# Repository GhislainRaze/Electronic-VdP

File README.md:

# An electronic Van der Pol/Duffing oscillator

## Overview
This repository contains files for the realization of an electronic Van der Pol/Duffing oscillator, i.e., a circuit whose behavior is governed the equation

$\qquad m\ddot{x}(t) + (\mu x^2(t)+c)\dot{x}(t) + kx(t) + k_3 x^3(t) = f_{ext}(t),$
    
with $m>0$ and $k_3\geq0$.

The circuit takes a signal proportional to $f_{ext}$ and the parameters $c$ and $\mu$ as input and outputs signals proportional to $x$ and $\dot{x}$. It allows for tunable values of the parameters $k$ and $k_3$ via the use of potentiometers. It is also possible to chose positive or negative values for $k$ and obtain a single- or double-well oscillator, respectively.

The circuit requires an external power source with symmetric supplies. The input and output signals can be imposed/measured with BNC connectors.

## References

The circuit diagrams were realized using KiCad7.0 (https://www.kicad.org/), inspired from the following works:

\[1\] B. K. Jones and G. Trefan, “The Duffing oscillator: A precise electronic analog chaos demonstrator for the undergraduate laboratory,” Am. J. Phys., vol. 69, no. 4, pp. 464–469, Apr. 2001, doi: [10.1119/1.1336838](https://doi.org/10.1119/1.1336838).

\[2\] K. Srinivasan, K. Thamilmaran, and A. Venkatesan, “Effect of nonsinusoidal periodic forces in Duffing oscillator: Numerical and analog simulation studies,” Chaos, Solitons & Fractals, vol. 40, no. 1, pp. 319–330, Apr. 2009, doi: [10.1016/j.chaos.2007.07.090](https://doi.org/10.1016/j.chaos.2007.07.090).

## More information

For more infomation, see the [documentation file](DOC/Electronic_VdP.pdf).

## License

<p xmlns:cc="http://creativecommons.org/ns#" >This work is licensed under <a href="http://creativecommons.org/licenses/by/4.0/?ref=chooser-v1" target="_blank" rel="license noopener noreferrer" style="display:inline-block;">CC BY 4.0</a></p>

## See also

[An electronic Duffing oscillator](https://github.com/GhislainRaze/Electronic-Duffing)

## Disclaimer

It is believed by the author that the design does not violate the Copyright of any other party. This cannot be guaranteed however, and the author accepts no liability for loss or damages that may be imposed upon the user by any Court of Law, statutory or other body, should it transpire that a similar circuit has been simultaneously or previously designed, published or patented by another party.

The author cannot be held responsible for any issues or damages either to life or property, or as monetary or physical losses, that might occur during the use of this circuit, either due to negligence, ignorance or lack of proper knowledge about the subject. It is entirely the user’s responsibility to determine the suitability of this design for the intended purpose, and to take enough precautions before assembling and using the circuit.

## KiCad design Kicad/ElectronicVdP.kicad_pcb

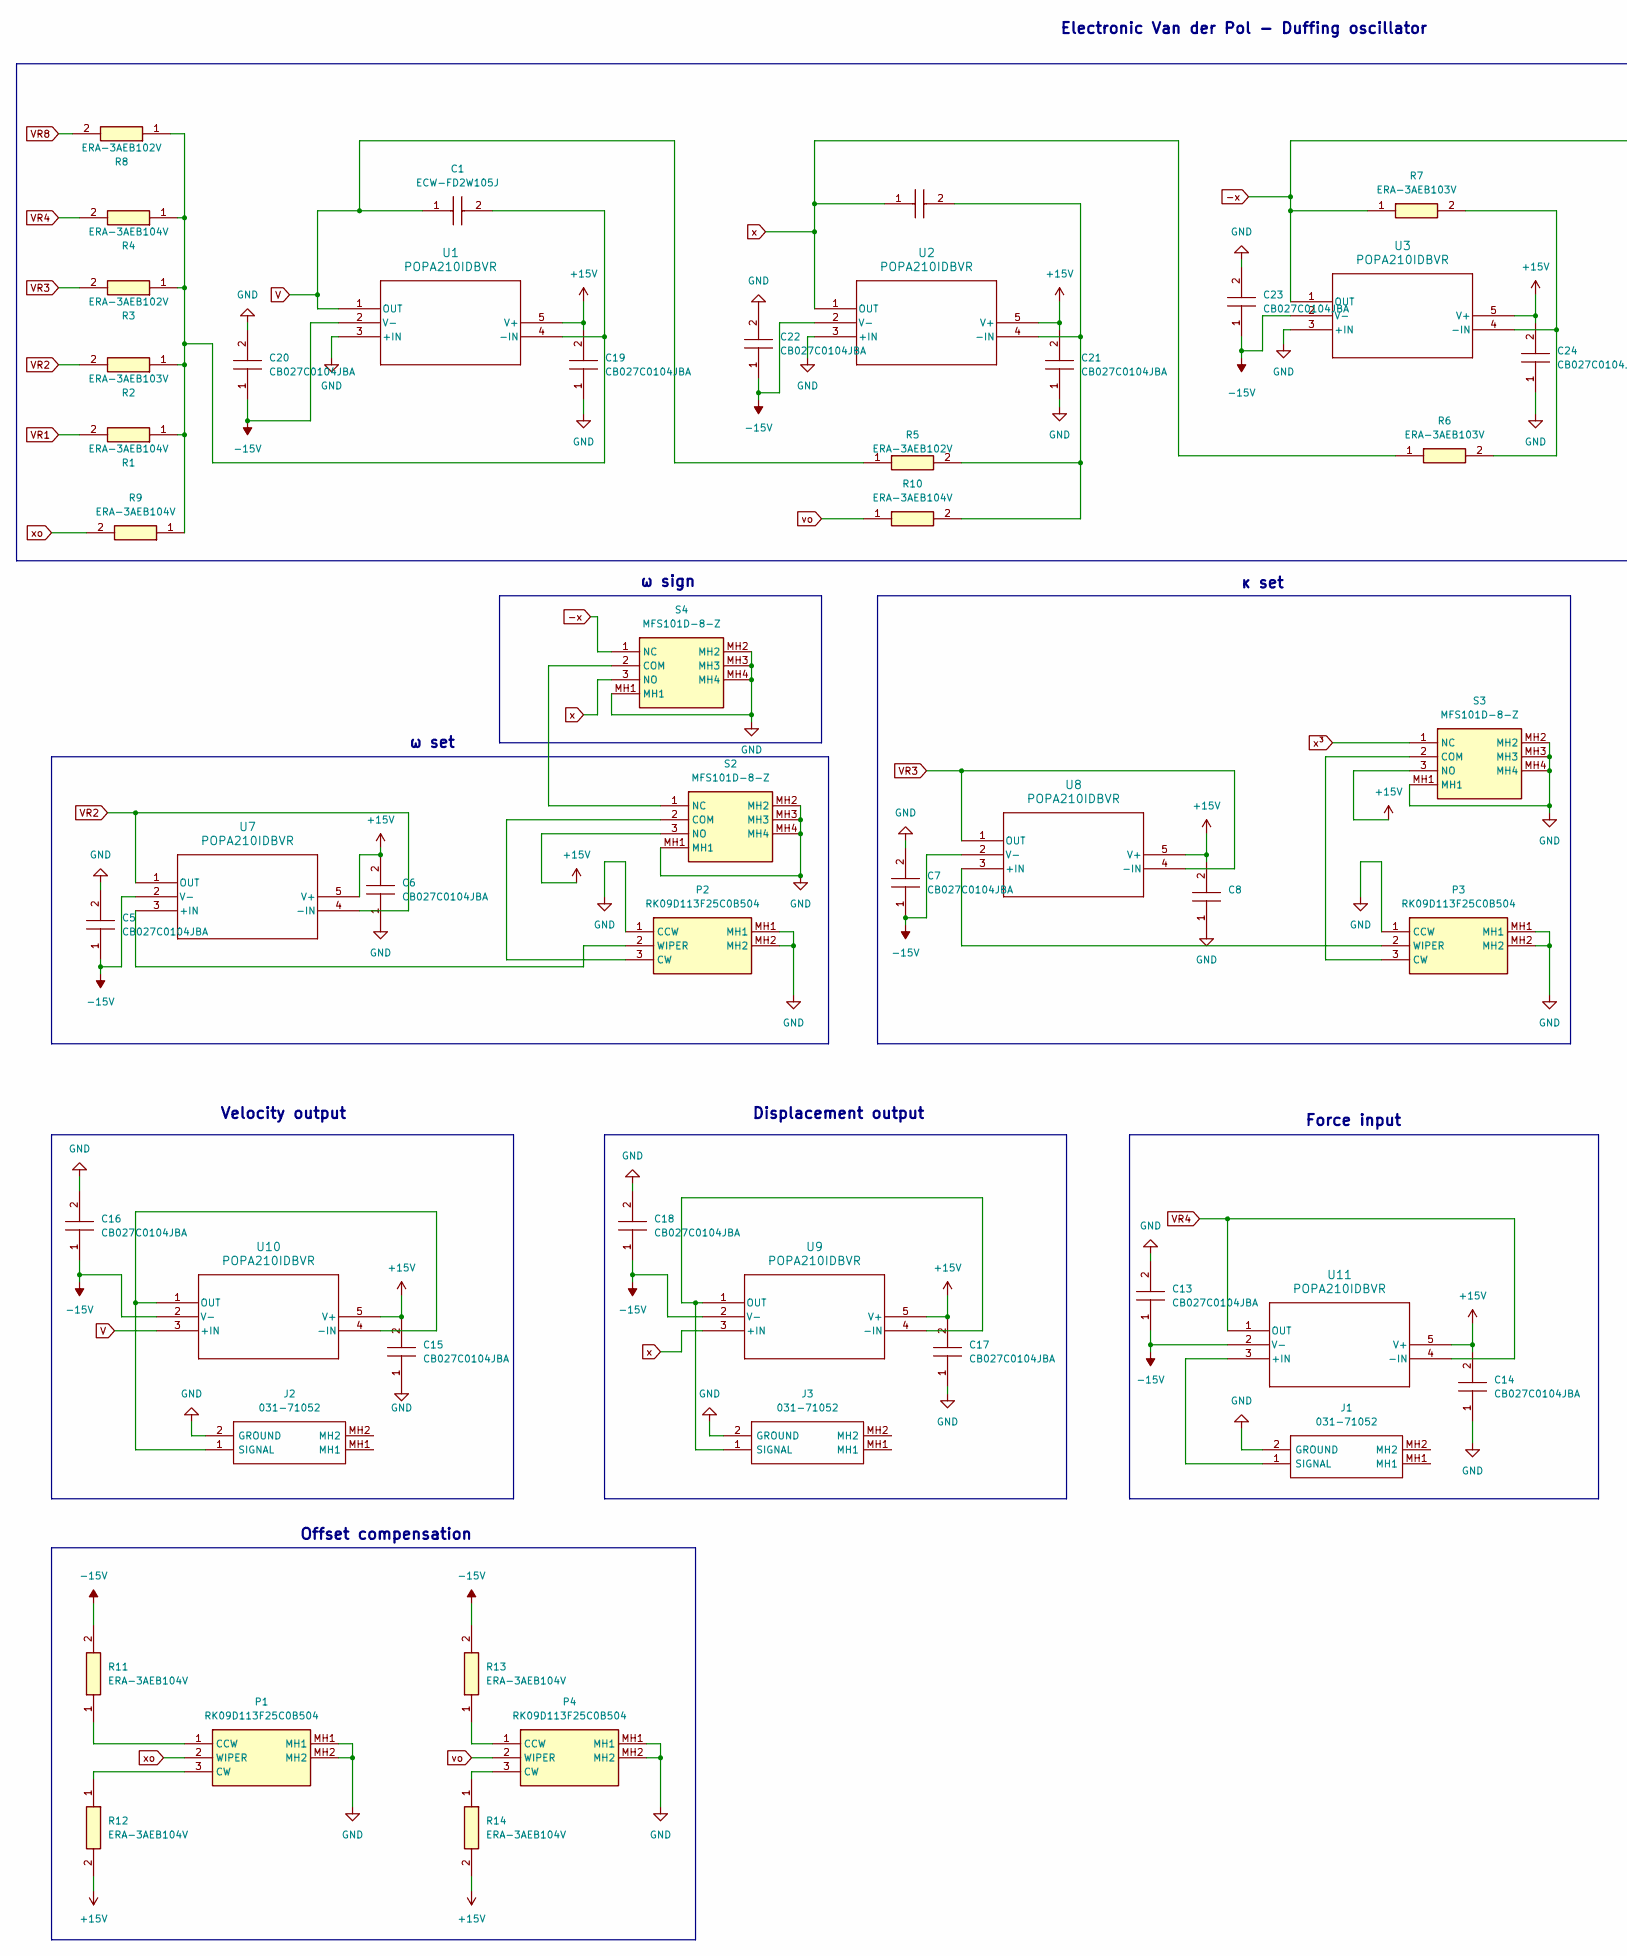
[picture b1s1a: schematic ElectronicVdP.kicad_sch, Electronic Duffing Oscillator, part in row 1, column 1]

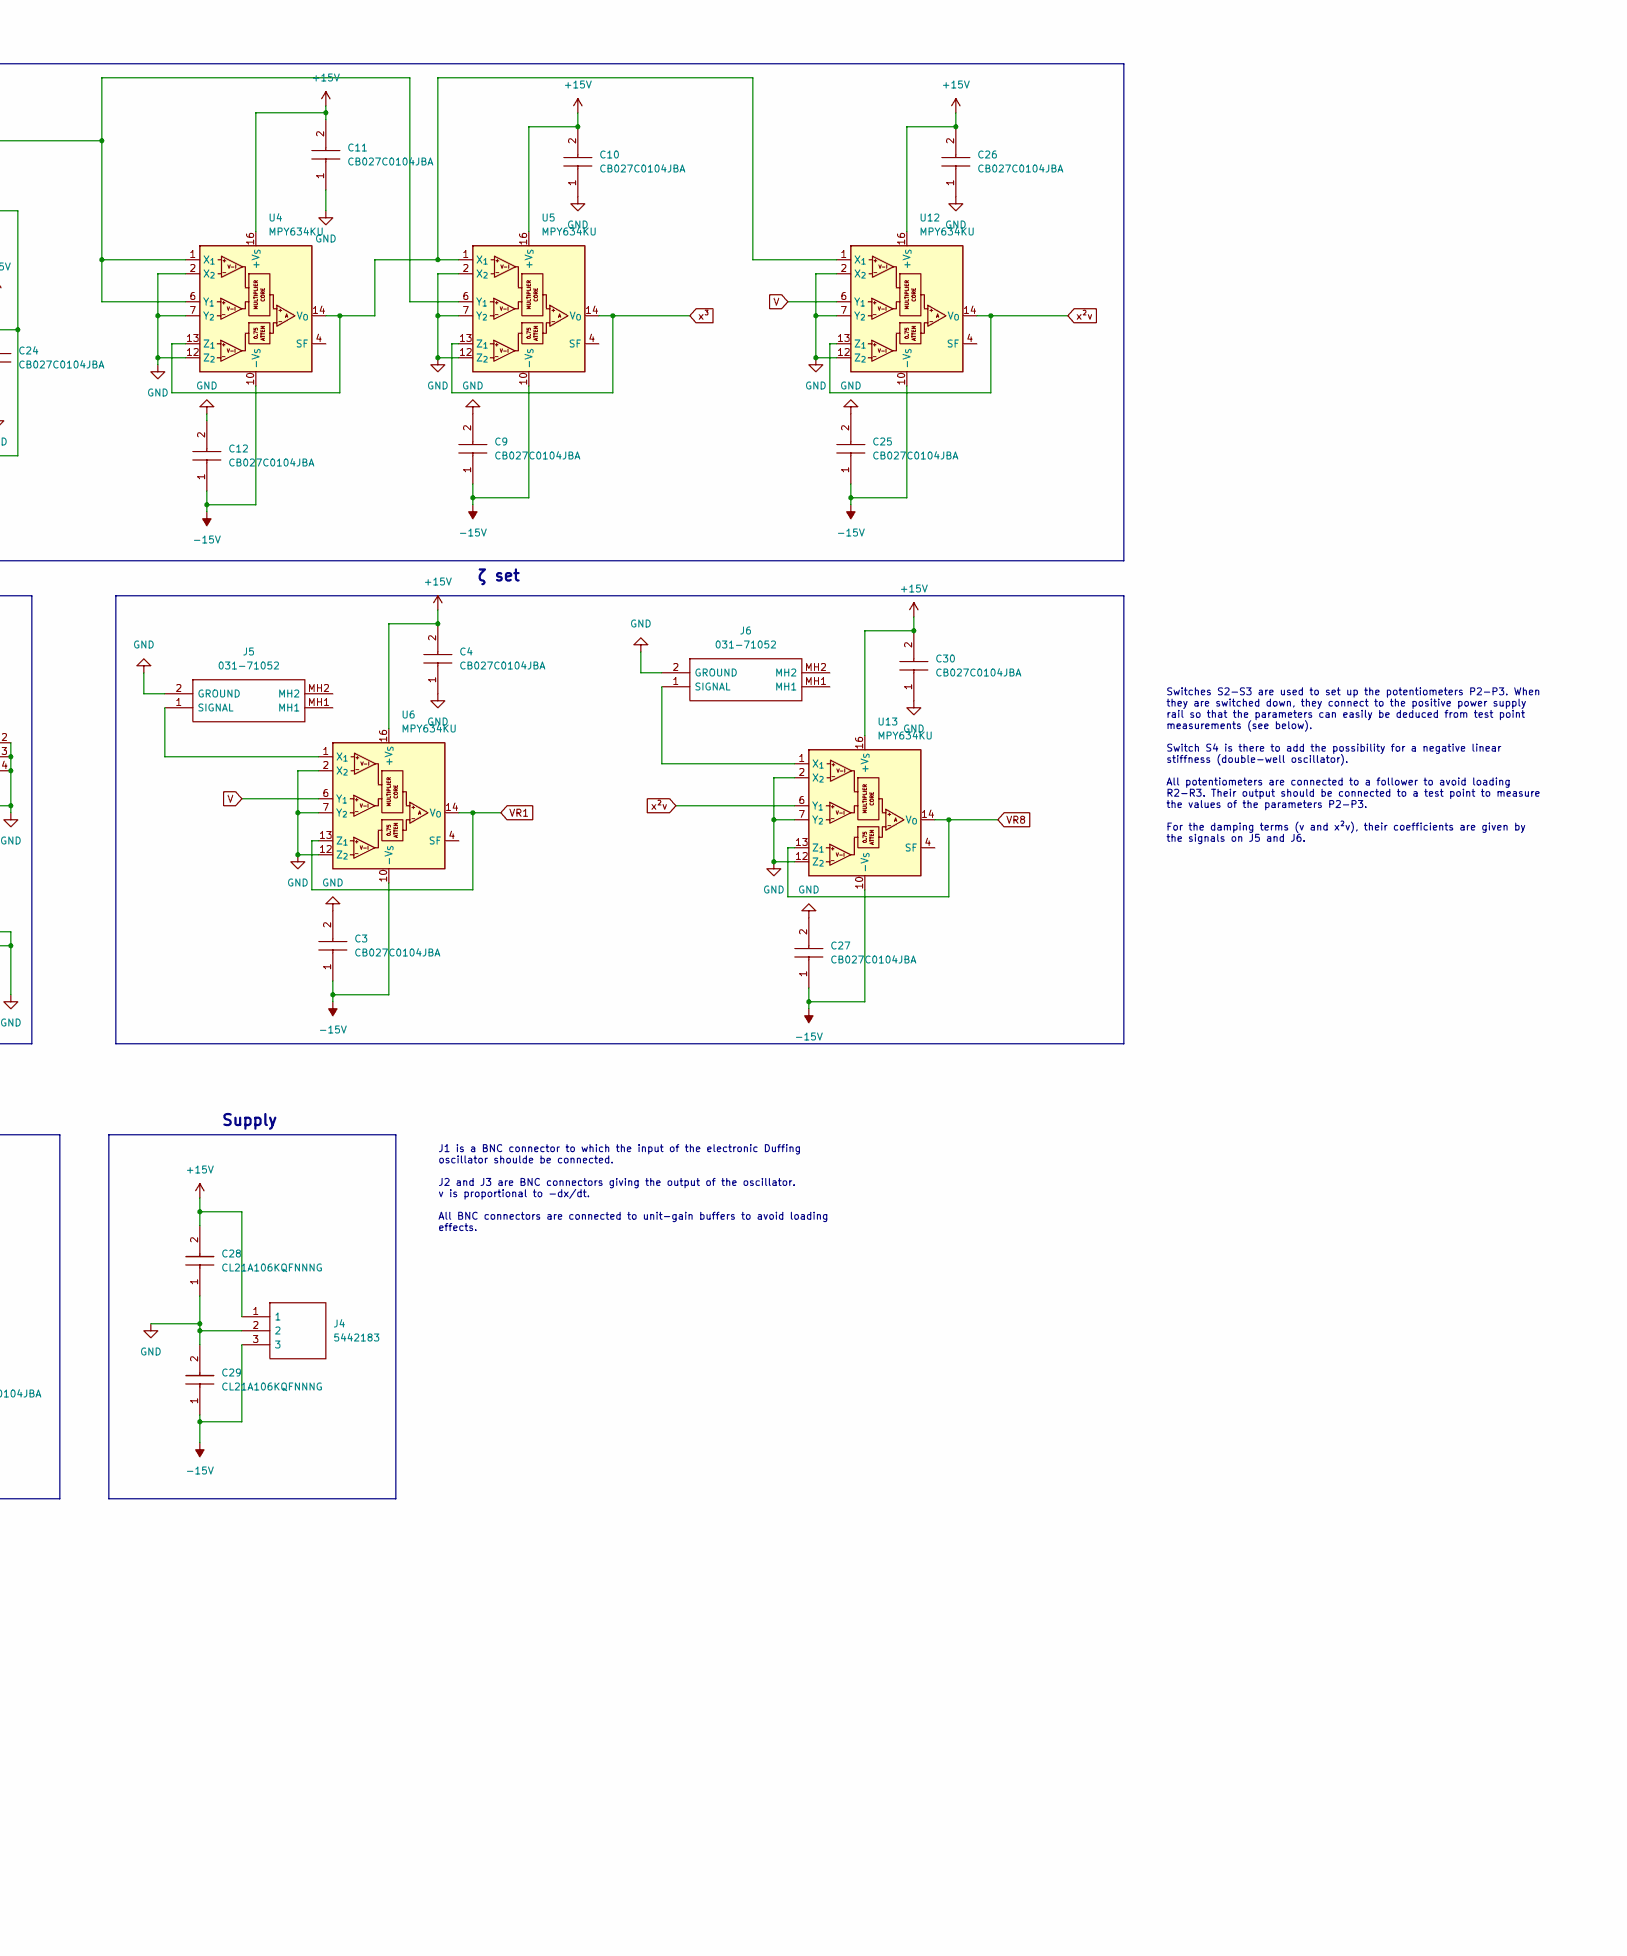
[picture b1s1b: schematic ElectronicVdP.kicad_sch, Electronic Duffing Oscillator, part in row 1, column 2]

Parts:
C1, C2: ECW-FD2W105J; ECWFD2W105J; Mouser Part Number 667-ECW-FD2W105J
C3, C4, C5, C6, C7, C8, C9, C10, C11, C12, C13, C14, C15, C16, C17, C18, C19, C20, C21, C22, C23, C24, C25, C26, C27, C30: CB027C0104JBA; CAPC3325X230N; Mouser Part Number 581-CB027C0104JBA
C28, C29: CL21A106KQFNNNG; CAPC2012X135N; Mouser Part Number 187-CL21A106KQFNNNG
J1, J2, J3, J5, J6: 031-71052; 03171052; Manufacturer_Part_Number 031-71052
J4: 5442183; Mouser Part Number 651-5442183
P1, P2, P3, P4: RK09D113F25C0B504; Mouser Part Number 688-RK09D113F25-500K
R1, R4, R9, R10, R11, R12, R13, R14: ERA-3AEB104V; ERA3AEB101V; Mouser Part Number 667-ERA-3AEB104V
R2, R6, R7: ERA-3AEB103V; ERA3AEB101V; Mouser Part Number 667-ERA-3AEB103V
R3, R5, R8: ERA-3AEB102V; ERA3AEB101V; Mouser Part Number 667-ERA-3AEB102V
S2, S3, S4: MFS101D-8-Z; MFS101D8Z; Mouser Part Number 229-MFS101D-8-Z
U1, U2, U3, U7, U8, U9, U10, U11: POPA210IDBVR; SOT23_DBV_TEX
U4, U5, U6, U12, U13: MPY634KU; SOIC-16W_7.5x10.3mm_P1.27mm

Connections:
+15V: C4.2, C6.2, C8.2, C10.2, C11.2, C14.2, C15.2, C17.2, C19.2, C21.2, C24.2, C26.2, C28.2, C30.2, J4.1, R12.2, R14.2, S2.3 (NO), S3.3 (NO), U1.5 (V+), U2.5 (V+), U3.5 (V+), U4.16 (+V_{S}), U5.16 (+V_{S}), U6.16 (+V_{S}), U7.5 (V+), U8.5 (V+), U9.5 (V+), U10.5 (V+), U11.5 (V+), U12.16 (+V_{S}), U13.16 (+V_{S})
-15V: C3.1, C5.1, C7.1, C9.1, C12.1, C13.1, C16.1, C18.1, C20.1, C22.1, C23.1, C25.1, C27.1, C29.1, J4.3, R11.2, R13.2, U1.2 (V-), U2.2 (V-), U3.2 (V-), U4.10 (-V_{S}), U5.10 (-V_{S}), U6.10 (-V_{S}), U7.2 (V-), U8.2 (V-), U9.2 (V-), U10.2 (V-), U11.2 (V-), U12.10 (-V_{S}), U13.10 (-V_{S})
-x: R7.1, S4.1 (NC), U3.1 (OUT), U4.1 (X_{1}), U4.6 (Y_{1}), U5.6 (Y_{1})
GND: C3.2, C4.1, C5.2, C6.1, C7.2, C8.1, C9.2, C10.1, C11.1, C12.2, C13.2, C14.1, C15.1, C16.2, C17.1, C18.2, C19.1, C20.2, C21.1, C22.2, C23.2, C24.1, C25.2, C26.1, C27.2, C28.1, C29.2, C30.1, J1.2 (GROUND), J2.2 (GROUND), J3.2 (GROUND), J4.2, J5.2 (GROUND), J6.2 (GROUND), P1.MH1, P1.MH2, P2.1 (CCW), P2.MH1, P2.MH2, P3.1 (CCW), P3.MH1, P3.MH2, P4.MH1, P4.MH2, S2.MH1, S2.MH2, S2.MH3, S2.MH4, S3.MH1, S3.MH2, S3.MH3, S3.MH4, S4.MH1, S4.MH2, S4.MH3, S4.MH4, U1.3 (+IN), U2.3 (+IN), U3.3 (+IN), U4.2 (X_{2}), U4.7 (Y_{2}), U4.12 (Z_{2}), U5.2 (X_{2}), U5.7 (Y_{2}), U5.12 (Z_{2}), U6.2 (X_{2}), U6.7 (Y_{2}), U6.12 (Z_{2}), U12.2 (X_{2}), U12.7 (Y_{2}), U12.12 (Z_{2}), U13.2 (X_{2}), U13.7 (Y_{2}), U13.12 (Z_{2})
unnamed: J1.1 (SIGNAL), U11.3 (+IN)
unnamed: J2.1 (SIGNAL), U10.1 (OUT), U10.4 (-IN)
unnamed: J3.1 (SIGNAL), U9.1 (OUT), U9.4 (-IN)
unnamed: J5.1 (SIGNAL), U6.1 (X_{1})
unnamed: J6.1 (SIGNAL), U13.1 (X_{1})
unnamed: P1.1 (CCW), R11.1
unnamed: P1.3 (CW), R12.1
unnamed: P2.3 (CW), S2.2 (COM)
unnamed: P2.2 (WIPER), U7.3 (+IN)
unnamed: P3.3 (CW), S3.2 (COM)
unnamed: P3.2 (WIPER), U8.3 (+IN)
unnamed: P4.1 (CCW), R13.1
unnamed: P4.3 (CW), R14.1
unnamed: S2.1 (NC), S4.2 (COM)
unnamed: C1.2, R1.1, R2.1, R3.1, R4.1, R8.1, R9.1, U1.4 (-IN)
unnamed: C2.2, R5.2, R10.2, U2.4 (-IN)
unnamed: R6.2, R7.2, U3.4 (-IN)
unnamed: U4.13 (Z_{1}), U4.14 (V_{O}), U5.1 (X_{1}), U12.1 (X_{1})
V: C1.1, R5.1, U1.1 (OUT), U6.6 (Y_{1}), U10.3 (+IN), U12.6 (Y_{1})
VR1: R1.2, U6.13 (Z_{1}), U6.14 (V_{O})
VR2: R2.2, U7.1 (OUT), U7.4 (-IN)
VR3: R3.2, U8.1 (OUT), U8.4 (-IN)
VR4: R4.2, U11.1 (OUT), U11.4 (-IN)
VR8: R8.2, U13.13 (Z_{1}), U13.14 (V_{O})
vo: P4.2 (WIPER), R10.1
x: C2.1, R6.1, S4.3 (NO), U2.1 (OUT), U9.3 (+IN)
xo: P1.2 (WIPER), R9.2
x²v: U12.13 (Z_{1}), U12.14 (V_{O}), U13.6 (Y_{1})
x³: S3.1 (NC), U5.13 (Z_{1}), U5.14 (V_{O})

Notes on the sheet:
ω set
Offset compensation
κ set
ω sign
Force input
J1 is a BNC connector to which the input of the electronic Duffing oscillator shoulde be connected. J2 and J3 are BNC connectors giving the output of the oscillator. v is proportional to -dx/dt. All BNC connectors are connected to unit-gain buffers to avoid loading effects.
Switches S2-S3 are used to set up the potentiometers P2-P3. When they are switched down, they connect to the positive power supply rail so that the parameters can easily be deduced from test point measurements (see below). Switch S4 is there to add the possibility for a negative linear stiffness (d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
ζ set
Supply
Displacement output
Velocity output
Electronic Van der Pol - Duffing oscillator

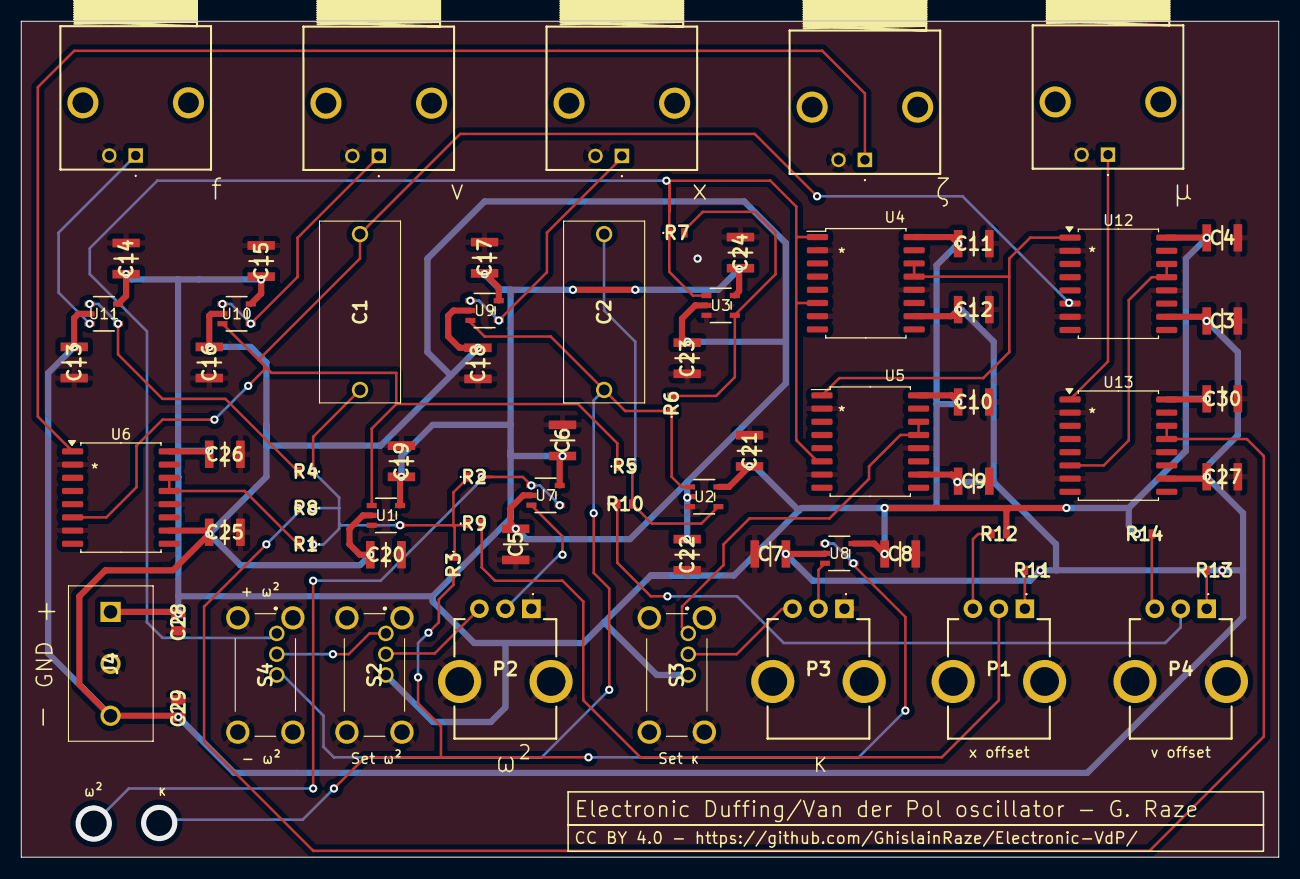
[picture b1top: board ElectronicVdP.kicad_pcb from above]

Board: 2 copper layers, 121.0 x 80.5 mm, 70 parts (0 on the bottom side), 33 nets.

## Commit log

2025-01-21 Create A
2025-01-21 Uploads

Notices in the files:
Kicad/ElectronicVdP.kicad_pcb:
CC BY 4.0 - https://github.com/GhislainRaze/Electronic-VdP
Kicad/ElectronicVdP.kicad_sch:
CC BY 4.0 - https://github.com/GhislainRaze/Electronic-Duffing
